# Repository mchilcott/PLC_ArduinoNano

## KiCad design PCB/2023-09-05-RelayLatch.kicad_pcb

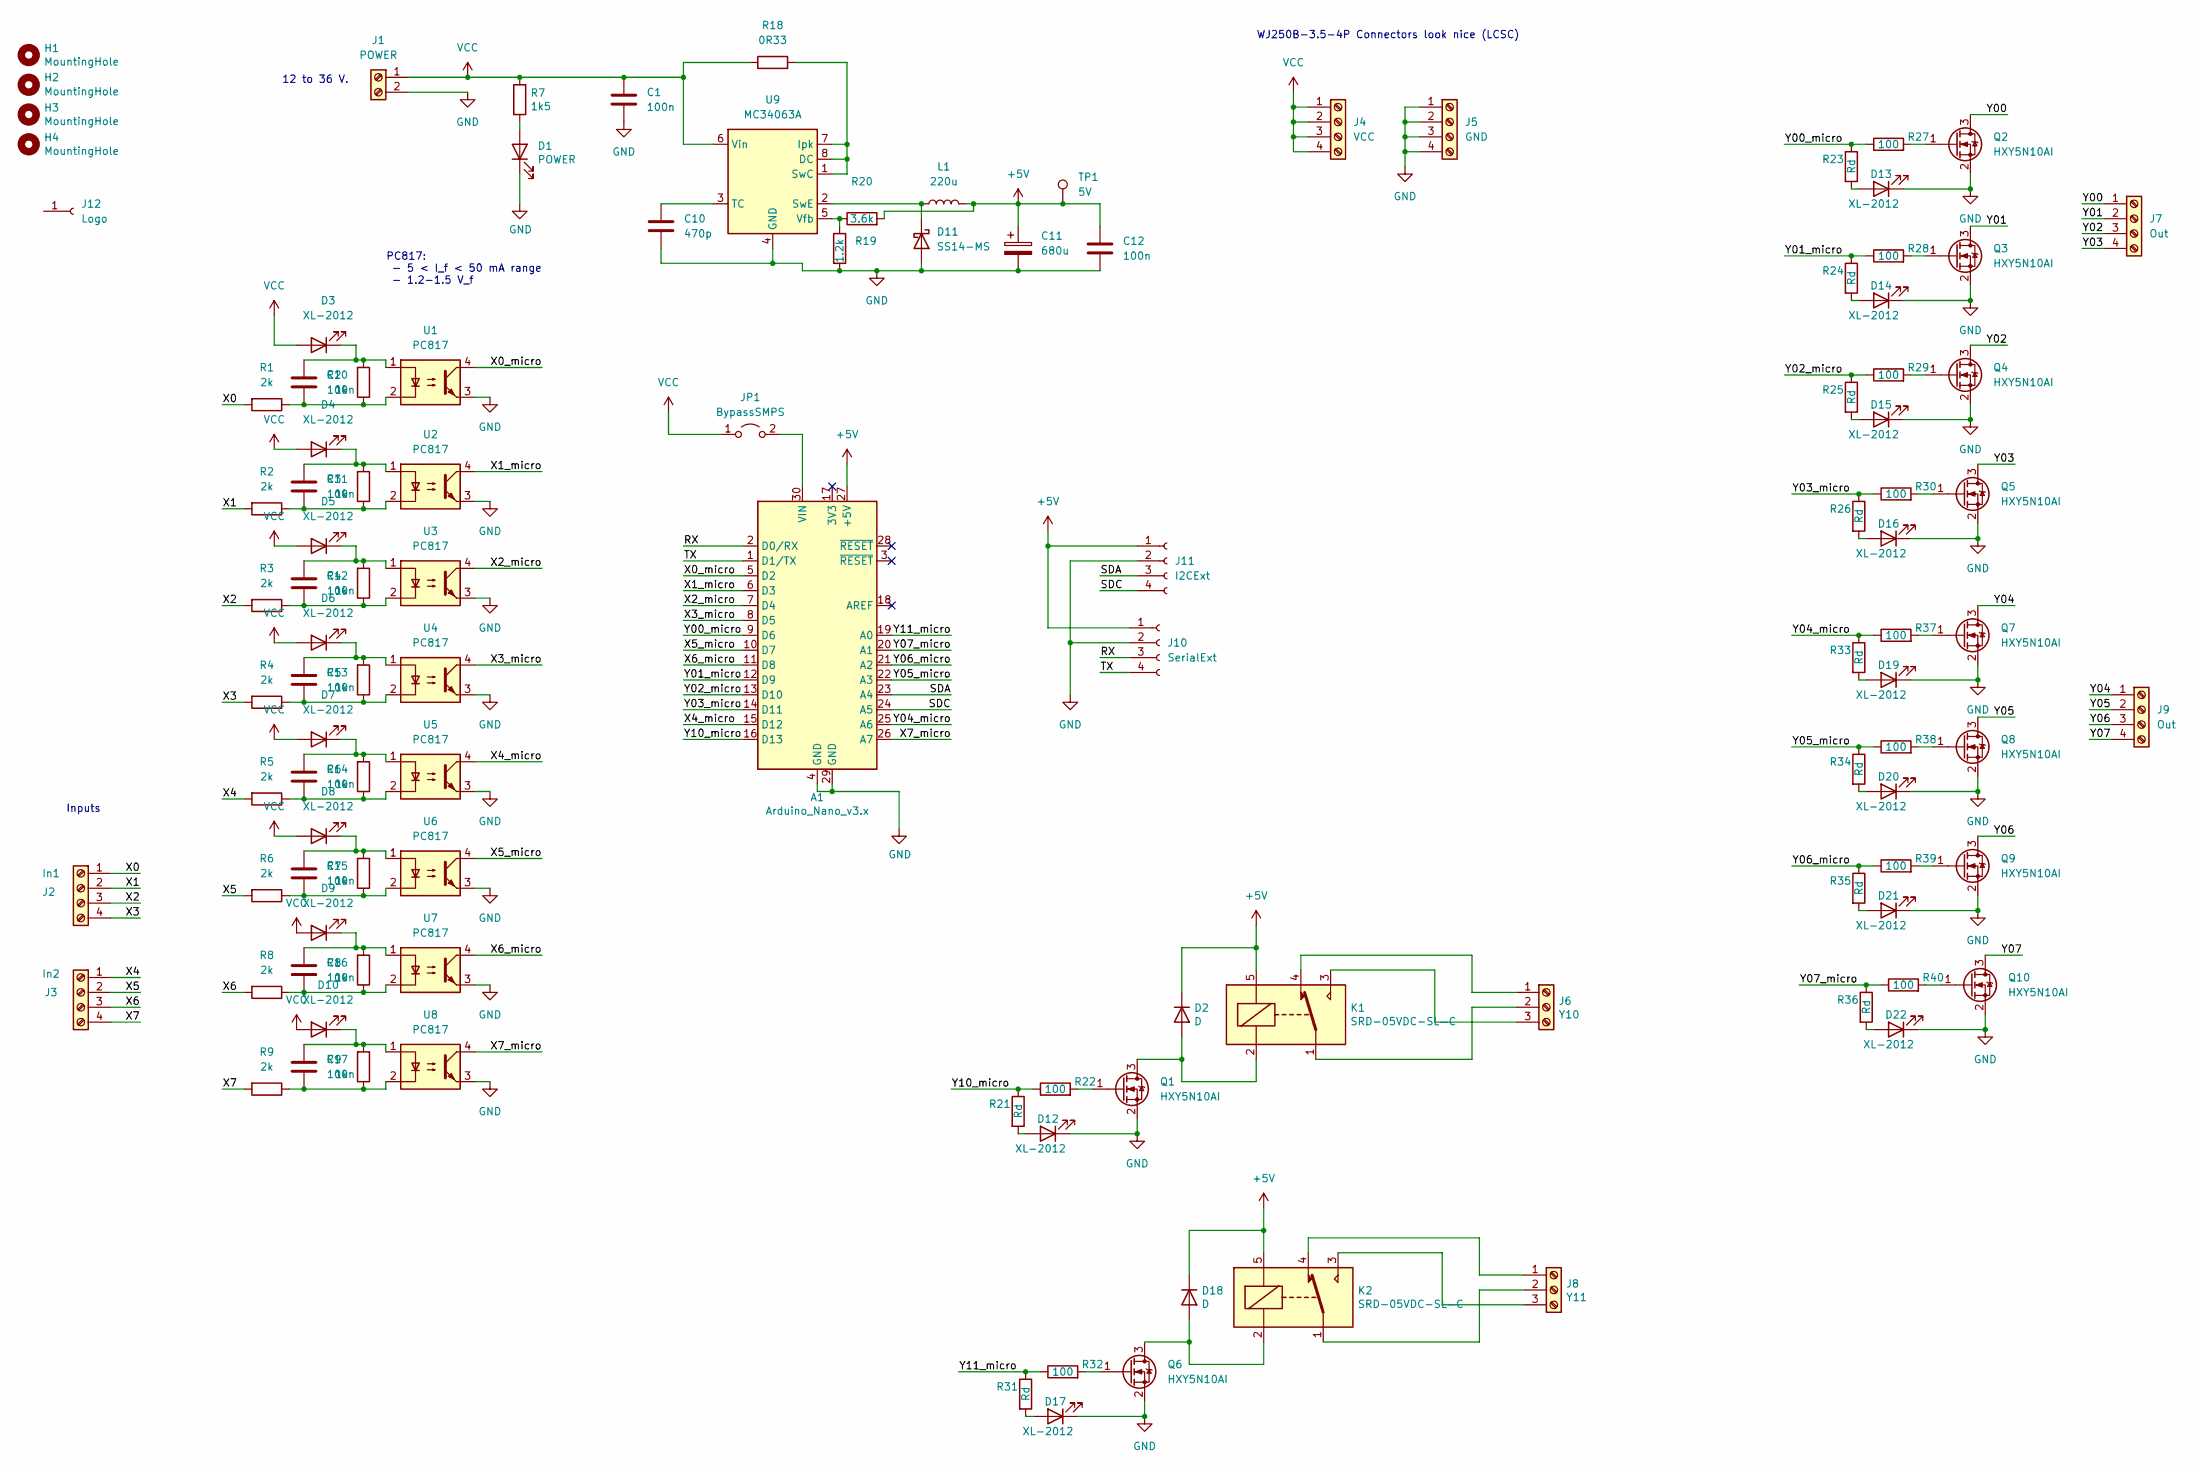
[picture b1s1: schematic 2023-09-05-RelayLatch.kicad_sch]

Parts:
A1: Arduino_Nano_v3.x; Arduino_Nano
C1, C2, C3, C4, C5, C6, C7, C8, C9, C12: 100n; C_0805_2012Metric
C10: 470p; C_0805_2012Metric
C11: 680u; C_Elec_8x10.2
D1: POWER; LED_0805_2012Metric
D2, D18: D; D_SMA; LCSCPart C95872
D3, D4, D5, D6, D7, D8, D9, D10, D12, D13, D14, D15, D16, D17, D19, D20, D21, D22: XL-2012; LED_0805_2012Metric
D11: SS14-MS; D_SMA; LCSCPart C2836394
H1, H2, H3, H4: MountingHole; MountingHole_3.2mm_M3_DIN965_Pad
J1: POWER; TerminalBlock_RND_205-00045_1x02_P5.00mm_Horizontal; LCSCPart C8404
J2: In1; TerminalBlock_RND_205-00047_1x04_P5.00mm_Horizontal
J3: In2; TerminalBlock_RND_205-00047_1x04_P5.00mm_Horizontal
J4: VCC; TerminalBlock_RND_205-00047_1x04_P5.00mm_Horizontal
J5: GND; TerminalBlock_RND_205-00047_1x04_P5.00mm_Horizontal
J6: Y10; TerminalBlock_RND_205-00046_1x03_P5.00mm_Horizontal; LCSCPart C8401
J7, J9: Out; TerminalBlock_RND_205-00047_1x04_P5.00mm_Horizontal
J8: Y11; TerminalBlock_RND_205-00046_1x03_P5.00mm_Horizontal
J10: SerialExt; PinHeader_1x04_P2.54mm_Vertical
J11: I2CExt; PinHeader_1x04_P2.54mm_Vertical
J12: Logo; MC
JP1: BypassSMPS; SolderJumper-2_P1.3mm_Open_RoundedPad1.0x1.5mm
K1, K2: SRD-05VDC-SL-C; Relay_SPDT_SANYOU_SRD_Series_Form_C; LCSCPart C35449
L1: 220u; L_Taiyo-Yuden_NR-80xx; LCSCPart C168148
Q1, Q2, Q3, Q4, Q5, Q6, Q7, Q8, Q9, Q10: HXY5N10AI; SOT-23; LCSCPart C3033404
R1, R2, R3, R4, R5, R6, R8, R9: 2k; R_0805_2012Metric
R7: 1k5; R_0805_2012Metric
R10, R11, R12, R13, R14, R15, R16, R17: 1k; R_0805_2012Metric
R18: 0R33; R_0805_2012Metric
R19: 1.2k; R_0805_2012Metric
R20: 3.6k; R_0805_2012Metric
R21, R23, R24, R25, R26, R31, R33, R34, R35, R36: Rd; R_0805_2012Metric
R22, R27, R28, R29, R30, R32, R37, R38, R39, R40: 100; R_0805_2012Metric
TP1: 5V; TestPoint_Pad_D1.5mm
U1, U2, U3, U4, U5, U6, U7, U8: PC817; DIP-4_W7.62mm; LCSCPart C7473156
U9: MC34063A; SOIC-8_3.9x4.9mm_P1.27mm; LCSCPart C18723538

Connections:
+5V: A1.27 (+5V), C11.1, C12.1, D2.1 (K), D18.1 (K), J10.1, J11.1, K1.5, K2.5, L1.2, R20.2, TP1.1
/RX: A1.2 (D0/RX), J10.3
/SDA: A1.23 (A4), J11.3
/SDC: A1.24 (A5), J11.4
/TX: A1.1 (D1/TX), J10.4
/X0: J2.1, R1.2
/X0_micro: A1.5 (D2), U1.4
/X1: J2.2, R2.2
/X1_micro: A1.6 (D3), U2.4
/X2: J2.3, R3.2
/X2_micro: A1.7 (D4), U3.4
/X3: J2.4, R4.2
/X3_micro: A1.8 (D5), U4.4
/X4: J3.1, R5.2
/X4_micro: A1.15 (D12), U5.4
/X5: J3.2, R6.2
/X5_micro: A1.10 (D7), U6.4
/X6: J3.3, R8.2
/X6_micro: A1.11 (D8), U7.4
/X7: J3.4, R9.2
/X7_micro: A1.26 (A7), U8.4
/Y00: J7.1, Q2.3 (D)
/Y00_micro: A1.9 (D6), R23.1, R27.1
/Y01: J7.2, Q3.3 (D)
/Y01_micro: A1.12 (D9), R24.1, R28.1
/Y02: J7.3, Q4.3 (D)
/Y02_micro: A1.13 (D10), R25.1, R29.1
/Y03: J7.4, Q5.3 (D)
/Y03_micro: A1.14 (D11), R26.1, R30.1
/Y04: J9.1, Q7.3 (D)
/Y04_micro: A1.25 (A6), R33.1, R37.1
/Y05: J9.2, Q8.3 (D)
/Y05_micro: A1.22 (A3), R34.1, R38.1
/Y06: J9.3, Q9.3 (D)
/Y06_micro: A1.21 (A2), R35.1, R39.1
/Y07: J9.4, Q10.3 (D)
/Y07_micro: A1.20 (A1), R36.1, R40.1
/Y10_micro: A1.16 (D13), R21.1, R22.1
/Y11_micro: A1.19 (A0), R31.1, R32.1
GND: A1.4 (GND), A1.29 (GND), C1.2, C10.2, C11.2, C12.2, D1.1 (K), D11.2 (A), D12.1 (K), D13.1 (K), D14.1 (K), D15.1 (K), D16.1 (K), D17.1 (K), D19.1 (K), D20.1 (K), D21.1 (K), D22.1 (K), J1.2, J5.1, J5.2, J5.3, J5.4, J10.2, J11.2, Q1.2 (S), Q2.2 (S), Q3.2 (S), Q4.2 (S), Q5.2 (S), Q6.2 (S), Q7.2 (S), Q8.2 (S), Q9.2 (S), Q10.2 (S), R19.2, U1.3, U2.3, U3.3, U4.3, U5.3, U6.3, U7.3, U8.3, U9.4 (GND)
unnamed: A1.30 (VIN), JP1.2 (B)
unnamed: C2.1, D3.1 (K), R10.2, U1.1
unnamed: C2.2, R1.1, R10.1, U1.2
unnamed: C3.1, D4.1 (K), R11.2, U2.1
unnamed: C3.2, R2.1, R11.1, U2.2
unnamed: C4.1, D5.1 (K), R12.2, U3.1
unnamed: C4.2, R3.1, R12.1, U3.2
unnamed: C5.1, D6.1 (K), R13.2, U4.1
unnamed: C5.2, R4.1, R13.1, U4.2
unnamed: C6.1, D7.1 (K), R14.2, U5.1
unnamed: C6.2, R5.1, R14.1, U5.2
unnamed: C7.1, D8.1 (K), R15.2, U6.1
unnamed: C7.2, R6.1, R15.1, U6.2
unnamed: C8.1, D9.1 (K), R16.2, U7.1
unnamed: C8.2, R8.1, R16.1, U7.2
unnamed: C9.1, D10.1 (K), R17.2, U8.1
unnamed: C9.2, R9.1, R17.1, U8.2
unnamed: C10.1, U9.3 (TC)
unnamed: D1.2 (A), R7.2
unnamed: D2.2 (A), K1.2, Q1.3 (D)
unnamed: D11.1 (K), L1.1, U9.2 (SwE)
unnamed: D12.2 (A), R21.2
unnamed: D13.2 (A), R23.2
unnamed: D14.2 (A), R24.2
unnamed: D15.2 (A), R25.2
unnamed: D16.2 (A), R26.2
unnamed: D17.2 (A), R31.2
unnamed: D18.2 (A), K2.2, Q6.3 (D)
unnamed: D19.2 (A), R33.2
unnamed: D20.2 (A), R34.2
unnamed: D21.2 (A), R35.2
unnamed: D22.2 (A), R36.2
unnamed: J6.1, K1.4
unnamed: J6.2, K1.1
unnamed: J6.3, K1.3
unnamed: J8.1, K2.4
unnamed: J8.2, K2.1
unnamed: J8.3, K2.3
unnamed: Q1.1 (G), R22.2
unnamed: Q2.1 (G), R27.2
unnamed: Q3.1 (G), R28.2
unnamed: Q4.1 (G), R29.2
unnamed: Q5.1 (G), R30.2
unnamed: Q6.1 (G), R32.2
unnamed: Q7.1 (G), R37.2
unnamed: Q8.1 (G), R38.2
unnamed: Q9.1 (G), R39.2
unnamed: Q10.1 (G), R40.2
unnamed: R18.2, U9.1 (SwC), U9.7 (Ipk), U9.8 (DC)
unnamed: R19.1, R20.1, U9.5 (Vfb)
VCC: C1.1, D3.2 (A), D4.2 (A), D5.2 (A), D6.2 (A), D7.2 (A), D8.2 (A), D9.2 (A), D10.2 (A), J1.1, J4.1, J4.2, J4.3, J4.4, JP1.1 (A), R7.1, R18.1, U9.6 (Vin)

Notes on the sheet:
Inputs
12 to 36 V.
PC817: - 5 < I_f < 50 mA range - 1.2-1.5 V_f
WJ250B-3.5-4P Connectors look nice (LCSC)

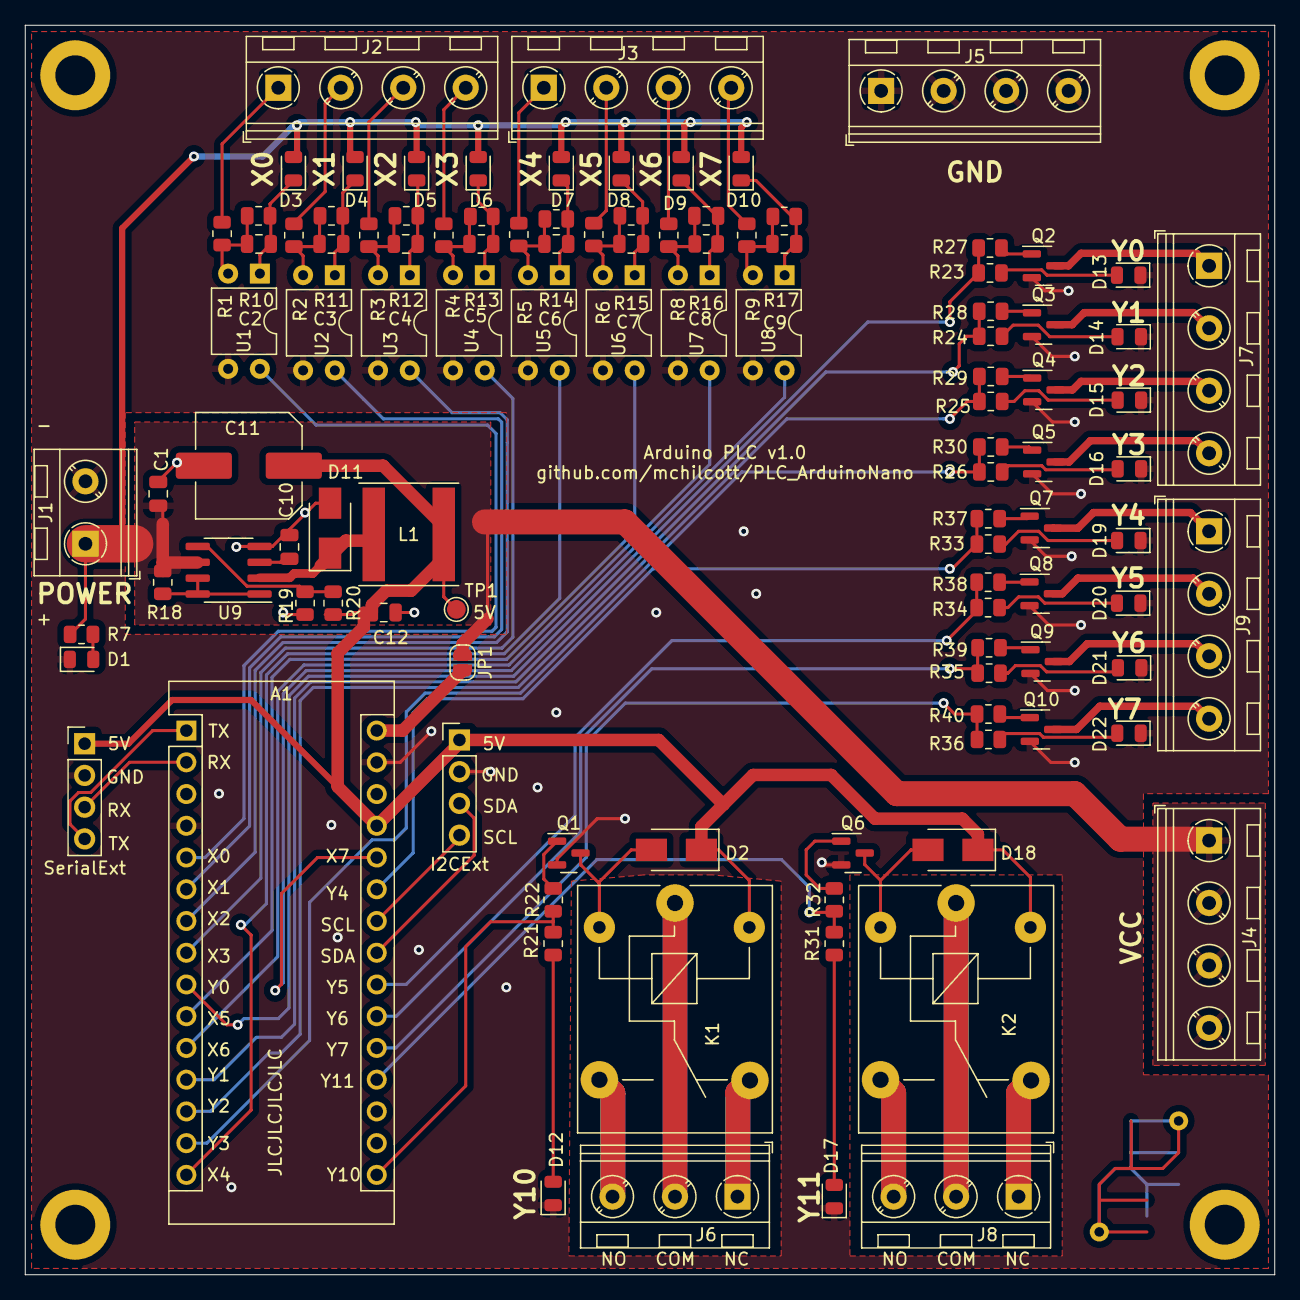
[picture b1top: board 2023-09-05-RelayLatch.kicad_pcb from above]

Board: 2 copper layers, 100.0 x 100.0 mm, 115 parts (0 on the bottom side), 91 nets.

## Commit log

2023-12-09 As manufactured for v1.0
